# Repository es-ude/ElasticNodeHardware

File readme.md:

# Elastic Node Hardware Platform

## ENv5 - Elastic Node v5
The 5th generation of Elastic node is designed based on the 4th version, but with some improvements. The main improvements are:
- Using Cortex-M0 MCU instead of AVR 8-bit MCU, to gain more performance and lower power consumption.
- Using SPI as the communication interface between MCU and the FPGA to save more IO pins.
- Simplify the power supply circuit to reduce the space and improve reliability.
- Adding an energy meter chip to ease the energy measurement.
- Optimize the PCB layout to reduce the PCB size.

Before you start using the ENv5, please read the following documents accordingly:
- [ENv5 Test Version User Manual](v5/test_version/readme.md)
- [ENv5 Revision 1 User Manual](v5/revision_1/readme.md)

Troubleshooting
- When you notice the esp32 is not responding to the RP2040, you can apply the [pre-build firmware](v5/revision_1/prebuilds-firmware/test_esp_at.uf2) to test.
  - some descriptions about the behavior of the test are available [here](v5/revision_1/prebuilds-firmware/readme.md).

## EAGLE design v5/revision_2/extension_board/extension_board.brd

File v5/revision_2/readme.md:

# ENv5 Revision 2 User Manual

## Notice:
- The old wifi-shield is not compatible with the ENv5-Rev1. Please use the new extension board instead.
  - When you plug out the extension board, please try to make to PCBs in parallel to avoid damage to the male headers.
- Before you plug in a battery to the ENv5, please check if the order of the battery is correct.
  - The Cable close to the dot sign should be positive.
  - A thermal resistor should be attached to the battery to prevent the battery from overheating. If the resistor is not soldered, don't use the battery.
- The pin mapping of Env5 is referred to the [schematic of env5-rev2](en_v5_rev2_schematic.pdf).
- The pin mapping of the extension board is referred to the [schematic of extension board](extension_board/extension_board_schematic.pdf).

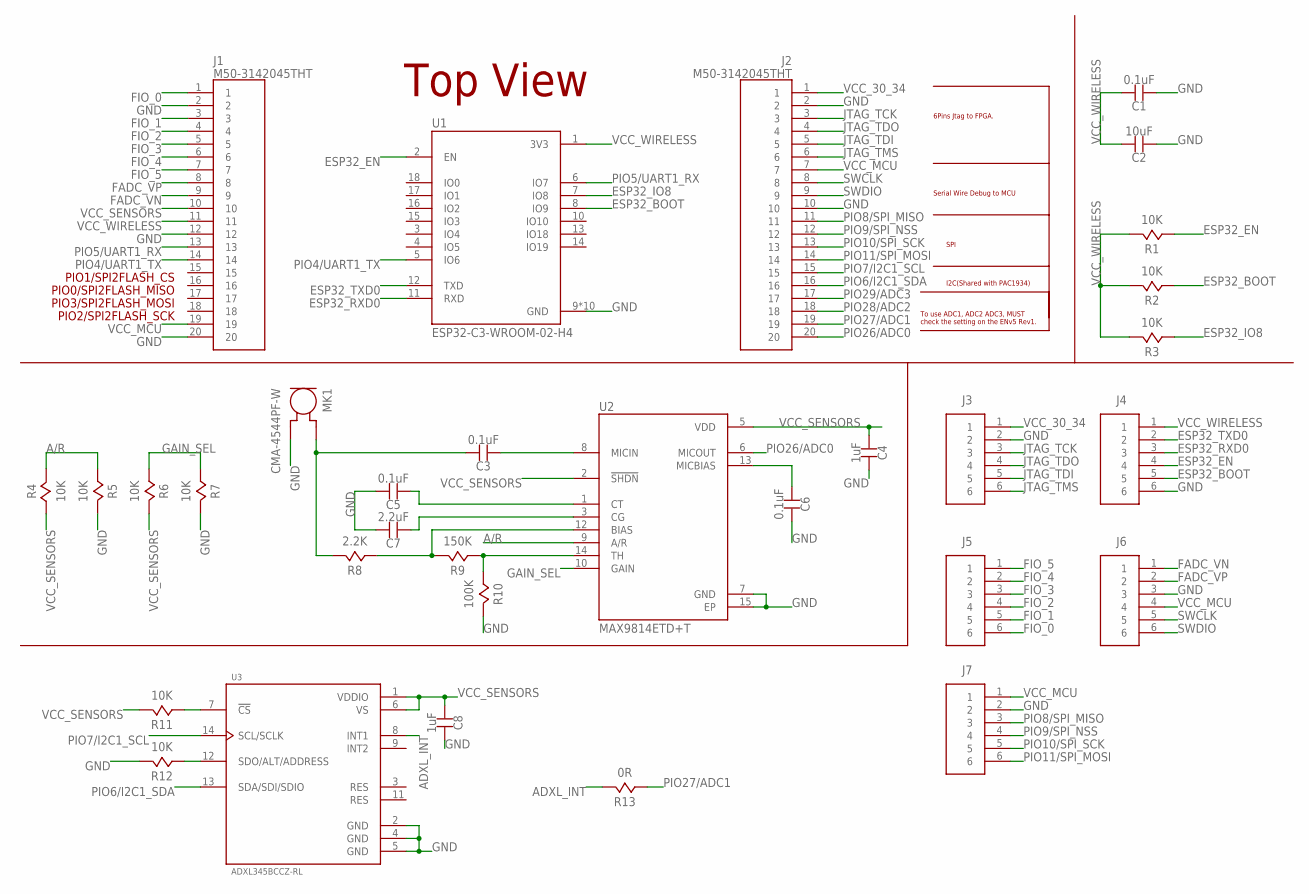
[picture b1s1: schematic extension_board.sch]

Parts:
C1, C3, C5, C6: 0.1uF; 0402
C2: 10uF; 0805
C4, C8: 1uF; 0402
C7: 2.2uF; 0402
J1, J2: M50-3142045THT; 20X1_HEADER_THT_1.27MM
J3, J4, J5, J6, J7: MALE_HEADER_6X1_2.54MM; HDR_6X1_2.54MM
MK1: CMA-4544PF-W; MIC_CMA-4544PF-W
R1, R2, R3, R4, R5, R6, R7, R11, R12: 10K; 0402
R8: 2.2K; 0402
R9: 150K; 0402
R10: 100K; 0402
R13: 0R; 0402
U1: ESP32-C3-WROOM-02-H4; MODULE_ESP32-C3-WROOM-02-H4
U2: MAX9814ETD+T; SON40P300X300X80-15N
U3: ADXL345BCCZ-RL; PQFN80P300X500X79-14N

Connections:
A/R: R4.2, R5.1, U2.9 (A/R)
ADXL_INT: R13.2, U3.8 (INT1)
ESP32_BOOT: J4.5, R2.1, U1.8 (IO9)
ESP32_EN: J4.4, R1.1, U1.2 (EN)
ESP32_IO8: R3.1, U1.7 (IO8)
ESP32_RXD0: J4.3, U1.11 (RXD)
ESP32_TXD0: J4.2, U1.12 (TXD)
FADC_VN: J1.9, J6.1
FADC_VP: J1.8, J6.2
FIO_0: J1.1, J5.6
FIO_1: J1.3, J5.5
FIO_2: J1.4, J5.4
FIO_3: J1.5, J5.3
FIO_4: J1.6, J5.2
FIO_5: J1.7, J5.1
GAIN_SEL: R6.1, R7.1, U2.10 (GAIN)
GND: C1.1, C2.1, C4.2, C5.2, C6.2, C7.2, C8.2, J1.2, J1.12, J1.20, J2.2, J2.10, J3.2, J4.6, J6.3, J7.2, MK1.2 (GND), R5.2, R7.2, R10.2, R12.2, U1.9 (GND), U1.19 (GND), U1.20 (GND), U1.21 (GND), U1.22 (GND), U1.23 (GND), U1.24 (GND), U1.25 (GND), U1.26 (GND), U1.27 (GND), U2.7 (GND), U2.15 (EP), U3.2 (GND), U3.4 (GND), U3.5 (GND)
JTAG_TCK: J2.3, J3.3
JTAG_TDI: J2.5, J3.5
JTAG_TDO: J2.4, J3.4
JTAG_TMS: J2.6, J3.6
MIC_INPUT: C3.2, MK1.1 (OUT), R8.2
unnamed: R11.1, U3.7 (!CS)
unnamed: R12.1, U3.12 (SDO/ALT/ADDRESS)
unnamed: C5.1, U2.1 (CT)
unnamed: C7.1, U2.3 (CG)
unnamed: C3.1, U2.8 (MICIN)
unnamed: R8.1, R9.2, U2.12 (BIAS)
unnamed: R9.1, R10.1, U2.14 (TH)
unnamed: C6.1, U2.13 (MICBIAS)
PIO4/UART1_TX: J1.14, U1.5 (IO6)
PIO5/UART1_RX: J1.13, U1.6 (IO7)
PIO6/I2C1_SDA: J2.16, U3.13 (SDA/SDI/SDIO)
PIO7/I2C1_SCL: J2.15, U3.14 (SCL/SCLK)
PIO8/SPI_MISO: J2.11, J7.3
PIO9/SPI_NSS: J2.12, J7.4
PIO10/SPI_SCK: J2.13, J7.5
PIO11/SPI_MOSI: J2.14, J7.6
PIO26/ADC0: J2.20, U2.6 (MICOUT)
PIO27/ADC1: J2.19, R13.1
PIO28/ADC2: J2.18
PIO29/ADC3: J2.17
SWCLK: J2.8, J6.5
SWDIO: J2.9, J6.6
VCC_30_34: J2.1, J3.1
VCC_MCU: J1.19, J2.7, J6.4, J7.1
VCC_SENSORS: C4.1, C8.1, J1.10, R4.1, R6.2, R11.2, U2.2 (!SHDN), U2.5 (VDD), U3.1 (VDDIO), U3.6 (VS)
VCC_WIRELESS: C1.2, C2.2, J1.11, J4.1, R1.2, R2.2, R3.2, U1.1 (3V3)

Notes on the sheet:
Top View
PIO1/SPI2FLASH_CS
PIO0/SPI2FLASH_MISO
PIO3/SPI2FLASH_MOSI
PIO2/SPI2FLASH_SCK
To use ADC1, ADC2 ADC3, MUST check the setting on the ENv5 Rev1.
6Pins Jtag to FPGA.
Serial Wire Debug to MCU
SPI
I2C(Shared with PAC1934)

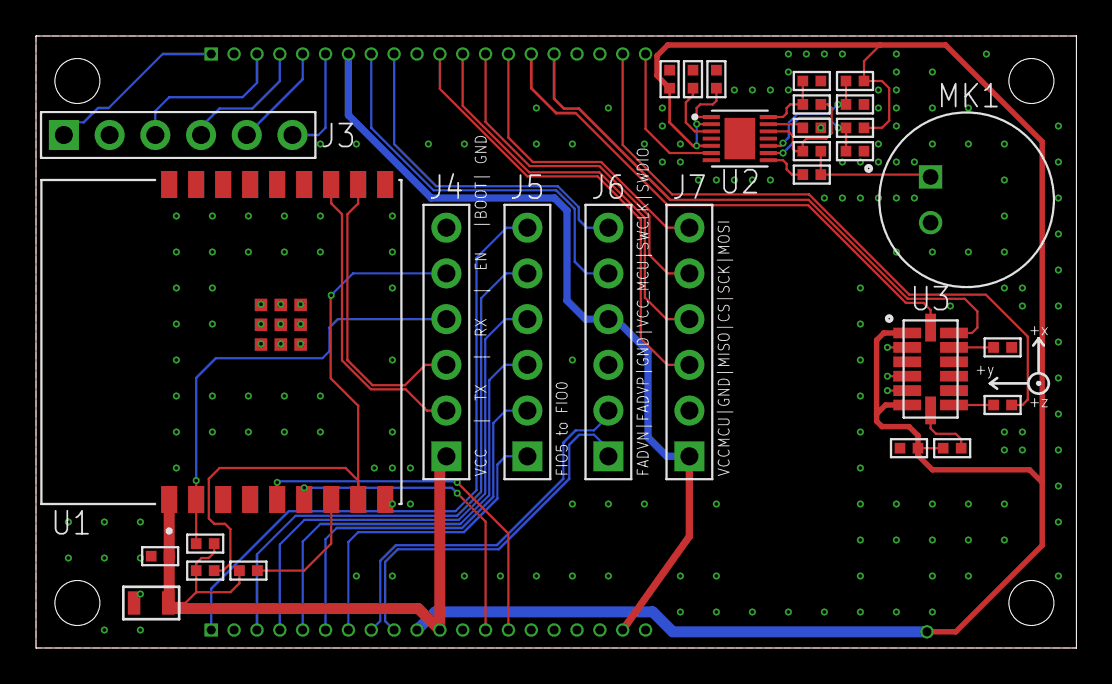
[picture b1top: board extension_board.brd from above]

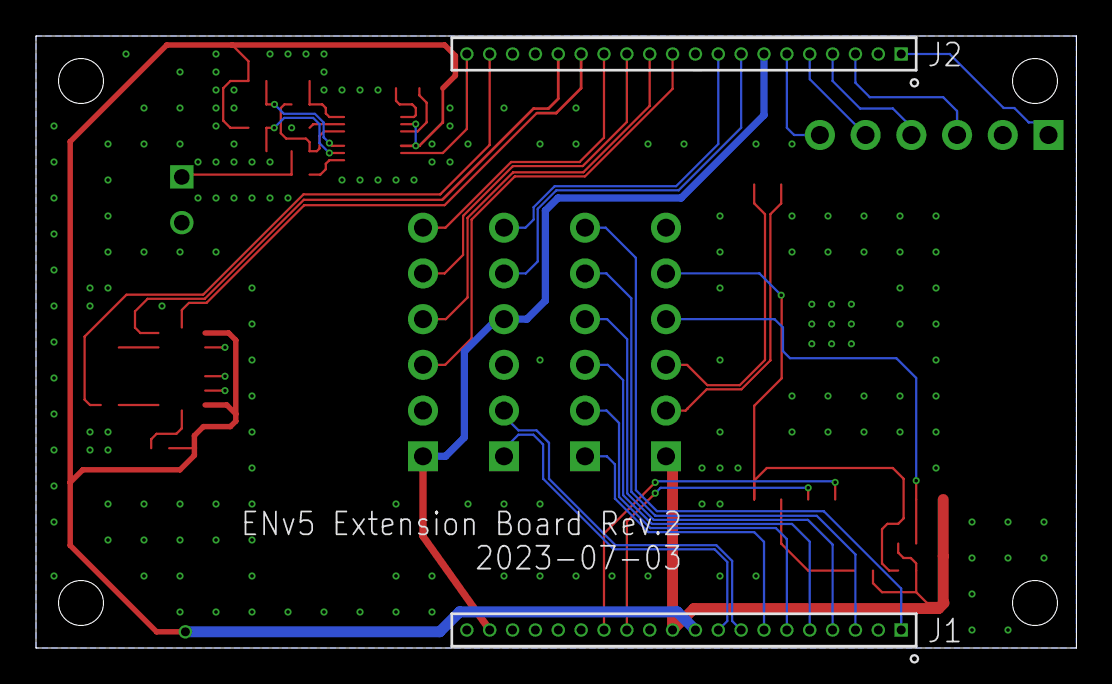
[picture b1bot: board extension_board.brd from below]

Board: 2 copper layers, 57.8 x 34.0 mm, 32 parts (2 on the bottom side), 46 nets.

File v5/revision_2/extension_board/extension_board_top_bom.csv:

Comment,Designator,Footprint,LCSC Part #
0.1uF,C1 C3 C5 C6,0402,
0R,R13,0402,
1uF,C4 C8,0402,
2.2K,R8,0402,
2.2uF,C7,0402,
10K,R1 R2 R3 R4 R5 R6 R7 R11 R12,0402,
10uF,C2,0805,
100K,R10,0402,
150K,R9,0402,
ADXL345BCCZ-RL,U3,PQFN80P300X500X79-14N,
ESP32-C3-WROOM-02-H4,U1,MODULE_ESP32-C3-WROOM-02-H4,
MAX9814ETD+T,U2,SON40P300X300X80-15N,

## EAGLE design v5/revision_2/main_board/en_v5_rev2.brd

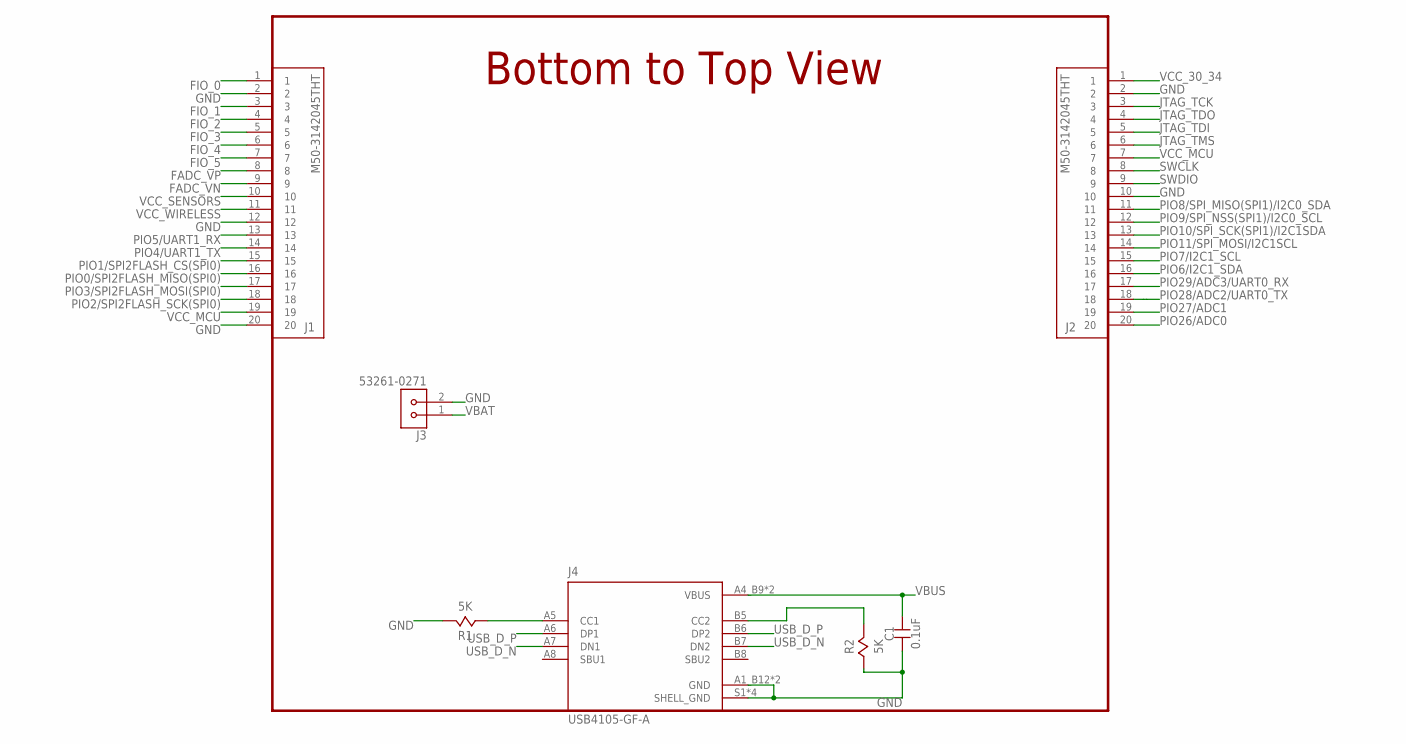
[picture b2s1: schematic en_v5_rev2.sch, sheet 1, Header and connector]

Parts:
C1: 0.1uF; 0805
J1, J2: M50-3142045THT; 20X1_HEADER_THT_1.27MM
J3: 53261-0271; MOLEX_53261-0271
J4: USB4105-GF-A; GCT_USB4105-GF-A
R1, R2: 5K; 0402

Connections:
FADC_VN: J1.9; also elsewhere on the board
FADC_VP: J1.8; also elsewhere on the board
FIO_0: J1.1; also elsewhere on the board
FIO_1: J1.3; also elsewhere on the board
FIO_2: J1.4; also elsewhere on the board
FIO_3: J1.5; also elsewhere on the board
FIO_4: J1.6; also elsewhere on the board
FIO_5: J1.7; also elsewhere on the board
GND: C1.1, J1.2, J1.12, J1.20, J2.2, J2.10, J3.2, J4.A1_B12 (GND), J4.B1_A12 (GND), J4.S1 (SHELL_GND), J4.S2 (SHELL_GND), J4.S3 (SHELL_GND), J4.S4 (SHELL_GND), R1.2, R2.1; also elsewhere on the board
JTAG_TCK: J2.3; also elsewhere on the board
JTAG_TDI: J2.5; also elsewhere on the board
JTAG_TDO: J2.4; also elsewhere on the board
JTAG_TMS: J2.6; also elsewhere on the board
unnamed: J4.B5 (CC2), R2.2
unnamed: J4.A5 (CC1), R1.1
PIO0/SPI2FLASH_MISO(SPI0): J1.16; also elsewhere on the board
PIO1/SPI2FLASH_CS(SPI0): J1.15; also elsewhere on the board
PIO2/SPI2FLASH_SCK(SPI0): J1.18; also elsewhere on the board
PIO3/SPI2FLASH_MOSI(SPI0): J1.17; also elsewhere on the board
PIO4/UART1_TX: J1.14; also elsewhere on the board
PIO5/UART1_RX: J1.13; also elsewhere on the board
PIO6/I2C1_SDA: J2.16; also elsewhere on the board
PIO7/I2C1_SCL: J2.15; also elsewhere on the board
PIO8/SPI_MISO(SPI1)/I2C0_SDA: J2.11; also elsewhere on the board
PIO9/SPI_NSS(SPI1)/I2C0_SCL: J2.12; also elsewhere on the board
PIO10/SPI_SCK(SPI1)/I2C1SDA: J2.13; also elsewhere on the board
PIO11/SPI_MOSI/I2C1SCL: J2.14; also elsewhere on the board
PIO26/ADC0: J2.20; also elsewhere on the board
PIO27/ADC1: J2.19; also elsewhere on the board
PIO28/ADC2/UART0_TX: J2.18; also elsewhere on the board
PIO29/ADC3/UART0_RX: J2.17; also elsewhere on the board
SWCLK: J2.8; also elsewhere on the board
SWDIO: J2.9; also elsewhere on the board
USB_D_N: J4.A7 (DN1), J4.B7 (DN2); also elsewhere on the board
USB_D_P: J4.A6 (DP1), J4.B6 (DP2); also elsewhere on the board
VBAT: J3.1; also elsewhere on the board
VBUS: C1.2, J4.A4_B9 (VBUS), J4.B4_A9 (VBUS); also elsewhere on the board
VCC_30_34: J2.1; also elsewhere on the board
VCC_MCU: J1.19, J2.7; also elsewhere on the board
VCC_SENSORS: J1.10; also elsewhere on the board
VCC_WIRELESS: J1.11; also elsewhere on the board

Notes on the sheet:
Bottom to Top View

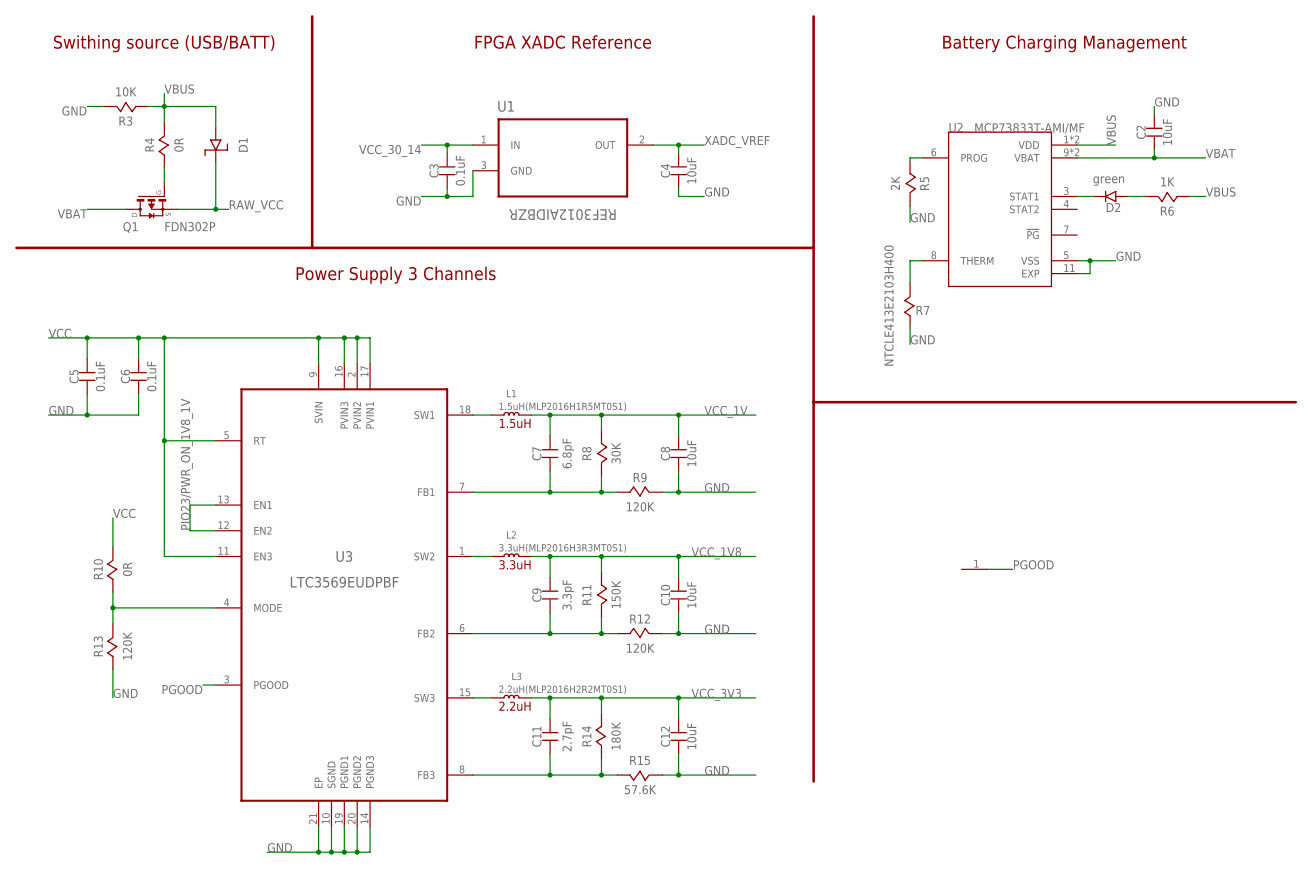
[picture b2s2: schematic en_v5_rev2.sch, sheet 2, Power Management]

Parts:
C2: 10uF; 0805
C3: 0.1uF; 0402
C4, C8, C10, C12: 10uF; CAPC1608-0603
C5, C6: 0.1uF; CAPC1608-0603
C7: 6.8pF; 0402
C9: 3.3pF; 0402
C11: 2.7pF; 0402
D1: DIODEB5817W; SOD-123
D2: green; 0402
L1: 1.5uH(MLP2016H1R5MT0S1); INDC2016X120N
L2: 3.3uH(MLP2016H3R3MT0S1); INDC2016X120N
L3: 2.2uH(MLP2016H2R2MT0S1); INDC2016X120N
Q1: FDN302P; SSOT-3
R3: 10K; 0402
R4, R10: 0R; 0402
R5: 2K; 0402
R6: 1K; 0402
R7: NTCLE413E2103H400; THT_2
R8: 30K; 0402
R9, R12, R13: 120K; 0402
R11: 150K; 0402
R14: 180K; 0402
R15: 57.6K; 0402
TP2: TEST_POINTSMD; SMD_PAD
U1: REF3012AIDBZR; SOT-23(3PIN)
U2: MCP73833T-AMI/MF; DFN-10(3X3X0.9)
U3: LTC3569EUDPBF; QFN40P300X300X80-21N

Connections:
GND: C2.2, C3.1, C4.1, C5.2, C6.2, C8.1, C10.2, C12.2, R3.2, R5.2, R7.P$1 (1), R9.2, R12.2, R13.1, R15.2, U1.3 (GND), U2.5 (VSS), U2.11 (EXP), U3.10 (SGND), U3.14 (PGND3), U3.19 (PGND1), U3.20 (PGND2), U3.21 (EP); also elsewhere on the board
unnamed: R7.P$2 (2), U2.8 (THERM)
unnamed: R5.1, U2.6 (PROG)
unnamed: Q1.1 (G), R4.1
unnamed: L2.1, U3.1 (SW2)
unnamed: L1.1, U3.18 (SW1)
unnamed: D2.2, U2.3 (STAT1)
unnamed: D2.1, R6.2
unnamed: C7.2, R8.2, R9.1, U3.7 (FB1)
unnamed: L3.2, U3.15 (SW3)
unnamed: C11.2, R14.2, R15.1, U3.8 (FB3)
unnamed: C9.2, R11.2, R12.1, U3.6 (FB2)
unnamed: R10.1, R13.2, U3.4 (MODE)
PGOOD: TP2.1, U3.3 (PGOOD)
PIO23/PWR_ON_1V8_1V: U3.12 (EN2), U3.13 (EN1); also elsewhere on the board
RAW_VCC: D1.1 (C), Q1.2 (S); also elsewhere on the board
VBAT: C2.1, Q1.3 (D), U2.9 (VBAT), U2.10 (VBAT); also elsewhere on the board
VBUS: D1.2 (A), R3.1, R4.2, R6.1, U2.1 (VDD), U2.2 (VDD); also elsewhere on the board
VCC: C5.1, C6.1, R10.2, U3.2 (PVIN2), U3.5 (RT), U3.9 (SVIN), U3.11 (EN3), U3.16 (PVIN3), U3.17 (PVIN1); also elsewhere on the board
VCC_1V: C7.1, C8.2, L1.2, R8.1; also elsewhere on the board
VCC_1V8: C9.1, C10.1, L2.2, R11.1; also elsewhere on the board
VCC_3V3: C11.1, C12.1, L3.1, R14.1; also elsewhere on the board
VCC_30_14: C3.2, U1.1 (IN); also elsewhere on the board
XADC_VREF: C4.2, U1.2 (OUT); also elsewhere on the board

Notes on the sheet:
1.5uH
3.3uH
2.2uH
Power Supply 3 Channels
Swithing source (USB/BATT)
FPGA XADC Reference
Battery Charging Management

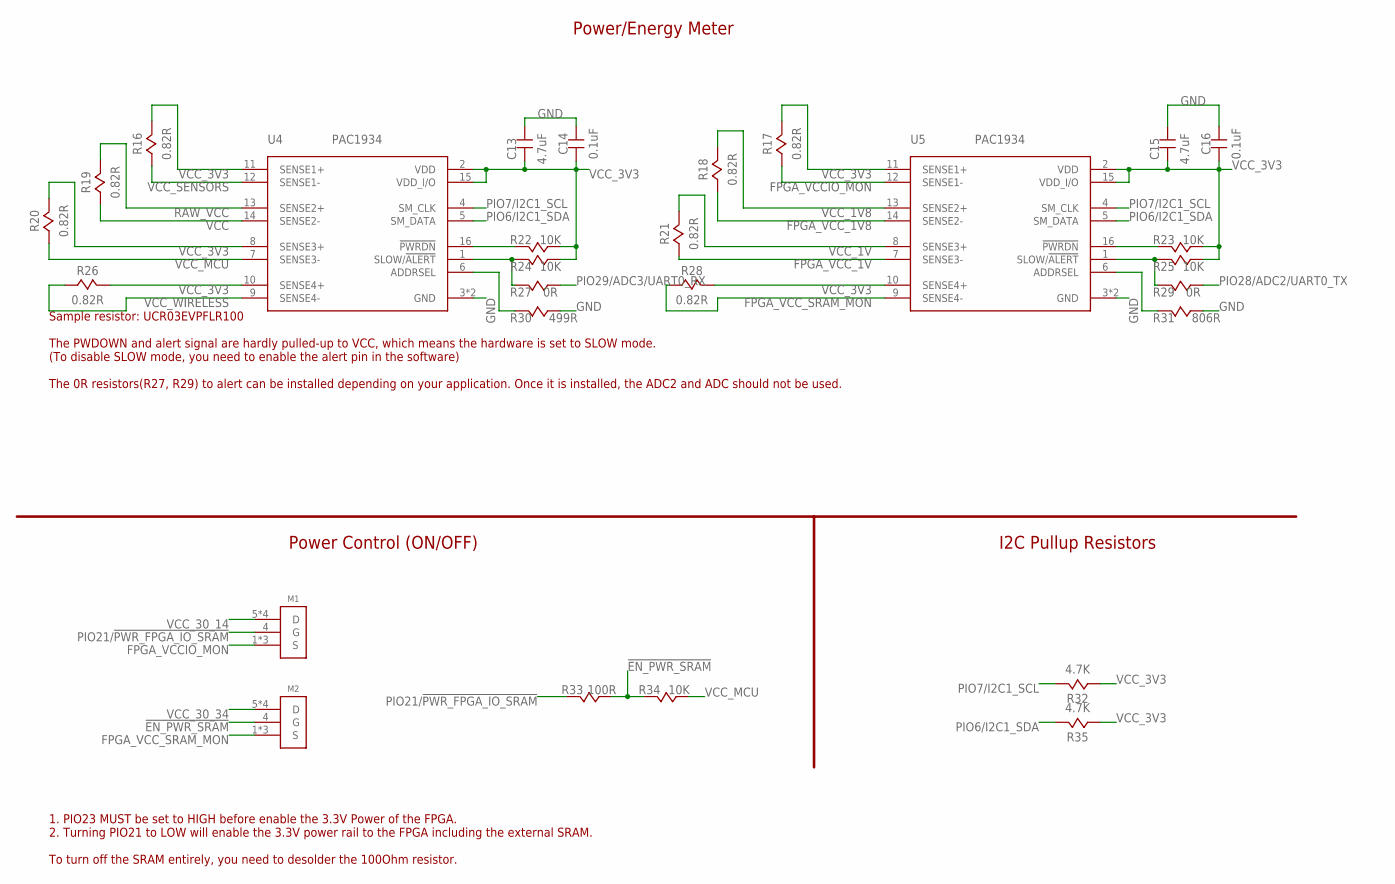
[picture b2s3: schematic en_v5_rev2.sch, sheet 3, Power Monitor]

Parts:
C13, C15: 4.7uF; CAPC1608-0603
C14, C16: 0.1uF; 0402
M1, M2: SISS23DN; POWERPAK1212-8
R16, R17, R18, R19, R20, R21, R26, R28: 0.82R; 0603
R22, R23, R24, R25, R34: 10K; 0402
R27, R29: 0R; 0402
R30: 499R; 0402
R31: 806R; 0402
R32, R35: 4.7K; 0402
R33: 100R; 0402
U4, U5: PAC1934; UQFN-16(4×4×0.5MM)

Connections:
!EN_PWR_SRAM: M2.4 (G), R33.1, R34.2
FPGA_VCCIO_MON: M1.1 (S), M1.2 (S), M1.3 (S), R17.1, U5.12 (SENSE1-)
FPGA_VCC_1V: R21.1, U5.7 (SENSE3-); also elsewhere on the board
FPGA_VCC_1V8: R18.1, U5.14 (SENSE2-); also elsewhere on the board
FPGA_VCC_SRAM_MON: M2.1 (S), M2.2 (S), M2.3 (S), R28.1, U5.9 (SENSE4-)
GND: C13.2, C14.2, C15.2, C16.2, R30.1, R31.1, U4.3 (GND), U4.17 (GND), U5.3 (GND), U5.17 (GND); also elsewhere on the board
unnamed: R24.2, R27.2, U4.1 (SLOW/!ALERT)
unnamed: R25.2, R29.2, U5.1 (SLOW/!ALERT)
unnamed: R22.2, U4.16 (!PWRDN)
unnamed: R30.2, U4.6 (ADDRSEL)
unnamed: R23.2, U5.16 (!PWRDN)
unnamed: R31.2, U5.6 (ADDRSEL)
PIO6/I2C1_SDA: R35.2, U4.5 (SM_DATA), U5.5 (SM_DATA); also elsewhere on the board
PIO7/I2C1_SCL: R32.2, U4.4 (SM_CLK), U5.4 (SM_CLK); also elsewhere on the board
PIO21/!PWR_FPGA_IO_SRAM: M1.4 (G), R33.2; also elsewhere on the board
PIO28/ADC2/UART0_TX: R29.1; also elsewhere on the board
PIO29/ADC3/UART0_RX: R27.1; also elsewhere on the board
RAW_VCC: R19.2, U4.13 (SENSE2+); also elsewhere on the board
VCC: R19.1, U4.14 (SENSE2-); also elsewhere on the board
VCC_1V: R21.2, U5.8 (SENSE3+); also elsewhere on the board
VCC_1V8: R18.2, U5.13 (SENSE2+); also elsewhere on the board
VCC_3V3: C13.1, C14.1, C15.1, C16.1, R16.2, R17.2, R20.2, R22.1, R23.1, R24.1, R25.1, R26.2, R28.2, R32.1, R35.1, U4.2 (VDD), U4.8 (SENSE3+), U4.10 (SENSE4+), U4.11 (SENSE1+), U4.15 (VDD_I/O), U5.2 (VDD), U5.10 (SENSE4+), U5.11 (SENSE1+), U5.15 (VDD_I/O); also elsewhere on the board
VCC_30_14: M1.5 (D), M1.6 (D), M1.7 (D), M1.8 (D); also elsewhere on the board
VCC_30_34: M2.5 (D), M2.6 (D), M2.7 (D), M2.8 (D); also elsewhere on the board
VCC_MCU: R20.1, R34.1, U4.7 (SENSE3-); also elsewhere on the board
VCC_SENSORS: R16.1, U4.12 (SENSE1-); also elsewhere on the board
VCC_WIRELESS: R26.1, U4.9 (SENSE4-); also elsewhere on the board

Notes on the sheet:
Sample resistor: UCR03EVPFLR100 The PWDOWN and alert signal are hardly pulled-up to VCC, which means the hardware is set to SLOW mode. (To disable SLOW mode, you need to enable the alert pin in the software) The 0R resistors(R27, R29) to alert can be installed depending on your application. Once it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
Power/Energy Meter
Power Control (ON/OFF)
I2C Pullup Resistors
1. PIO23 MUST be set to HIGH before enable the 3.3V Power of the FPGA. 2. Turning PIO21 to LOW will enable the 3.3V power rail to the FPGA including the external SRAM. To turn off the SRAM entirely, you need to desolder the 100Ohm resistor.

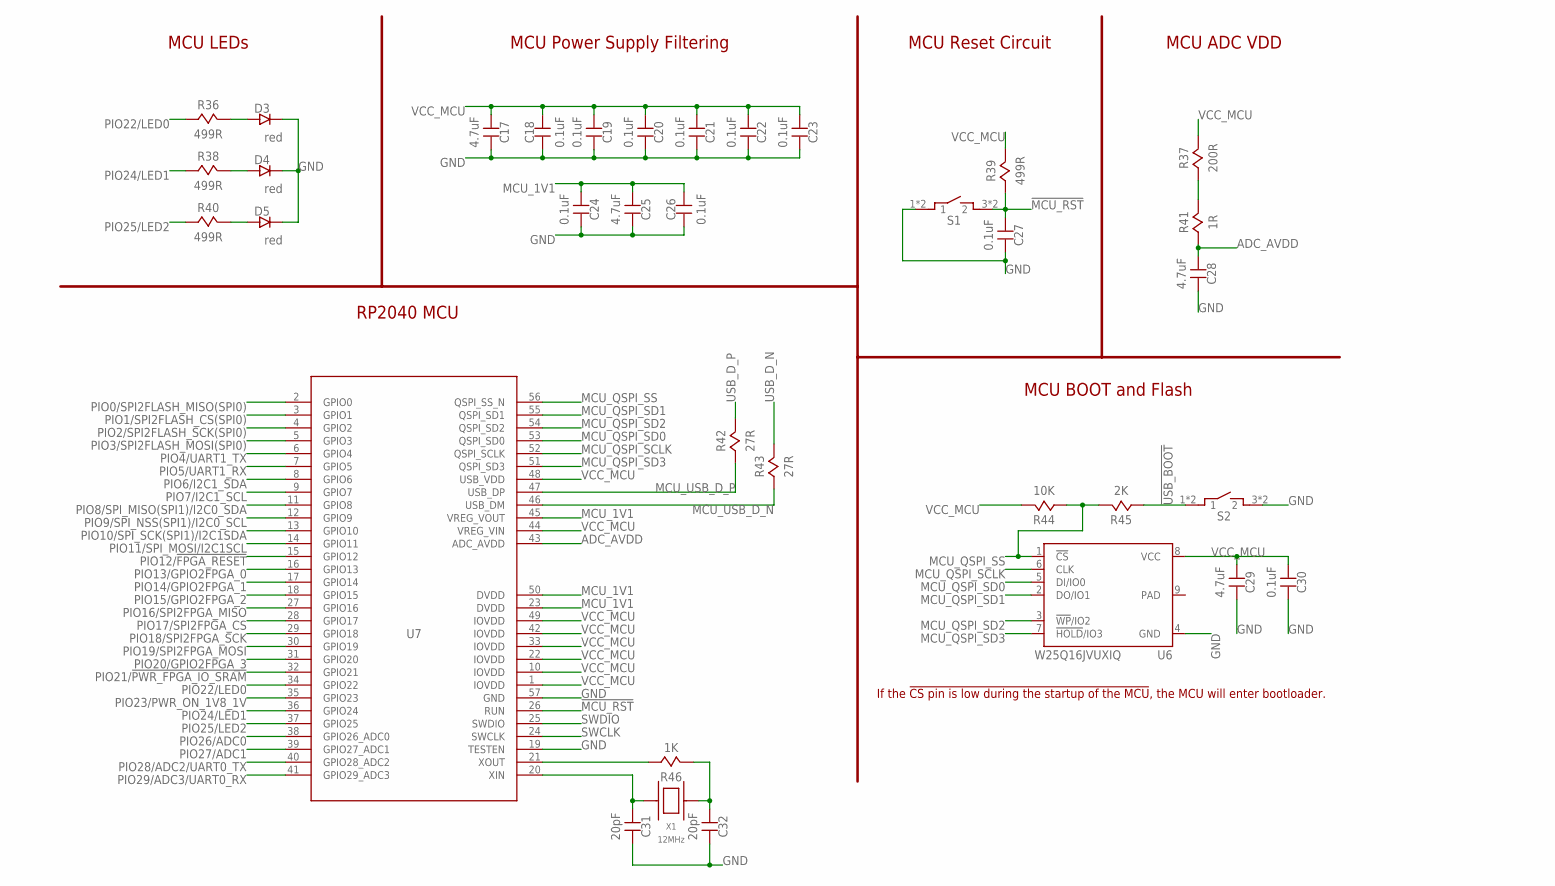
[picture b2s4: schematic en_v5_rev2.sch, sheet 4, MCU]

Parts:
C17, C25, C28, C29: 4.7uF; CAPC1608-0603
C18, C19, C20, C21, C22, C23, C24, C26, C27, C30: 0.1uF; 0402
C31, C32: 20pF; 0402
D3, D4, D5: red; 0402
R36, R38, R39, R40: 499R; 0402
R37: 200R; 0402
R41: 1R; 0402
R42, R43: 27R; 0402
R44: 10K; 0402
R45: 2K; 0402
R46: 1K; 0402
S1, S2: TACTILE-SWITCH
U6: W25Q16JVUXIQ; USON8-2X3MM
U7: RP2040; QFN40P700X700X100-57T310N
X1: 12MHz; 3.2X2.5_OSC

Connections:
!MCU_RST: C27.1, R39.1, S1.3 (2), S1.4 (2), U7.26 (RUN)
!USB_BOOT: R45.1, S2.1, S2.2 (1)
ADC_AVDD: C28.1, R41.1, U7.43 (ADC_AVDD)
ADC_VREF: R37.1, R41.2
GND: C17.2, C18.1, C19.2, C20.2, C21.2, C22.2, C23.2, C24.2, C25.2, C26.1, C27.2, C28.2, C29.2, C30.2, C31.2, C32.2, D3.2, D4.2, D5.2, S1.1, S1.2 (1), S2.3 (2), S2.4 (2), U6.4 (GND), U7.19 (TESTEN), U7.57 (GND); also elsewhere on the board
MCU_1V1: C24.1, C25.1, C26.2, U7.23 (DVDD), U7.45 (VREG_VOUT), U7.50 (DVDD)
MCU_QSPI_SCLK: U6.6 (CLK), U7.52 (QSPI_SCLK)
MCU_QSPI_SD0: U6.5 (DI/IO0), U7.53 (QSPI_SD0)
MCU_QSPI_SD1: U6.2 (DO/IO1), U7.55 (QSPI_SD1)
MCU_QSPI_SD2: U6.3 (!WP!/IO2), U7.54 (QSPI_SD2)
MCU_QSPI_SD3: U6.7 (!HOLD!/IO3), U7.51 (QSPI_SD3)
MCU_QSPI_SS: R44.1, R45.2, U6.1 (!CS), U7.56 (QSPI_SS_N)
MCU_USB_D_N: R43.1, U7.46 (USB_DM)
MCU_USB_D_P: R42.1, U7.47 (USB_DP)
unnamed: R46.1, U7.21 (XOUT)
unnamed: C32.1, R46.2, X1.3
unnamed: C31.1, U7.20 (XIN), X1.1
unnamed: D3.1, R36.2
unnamed: D4.1, R38.2
unnamed: D5.1, R40.2
PIO0/SPI2FLASH_MISO(SPI0): U7.2 (GPIO0); also elsewhere on the board
PIO1/SPI2FLASH_CS(SPI0): U7.3 (GPIO1); also elsewhere on the board
PIO2/SPI2FLASH_SCK(SPI0): U7.4 (GPIO2); also elsewhere on the board
PIO3/SPI2FLASH_MOSI(SPI0): U7.5 (GPIO3); also elsewhere on the board
PIO4/UART1_TX: U7.6 (GPIO4); also elsewhere on the board
PIO5/UART1_RX: U7.7 (GPIO5); also elsewhere on the board
PIO6/I2C1_SDA: U7.8 (GPIO6); also elsewhere on the board
PIO7/I2C1_SCL: U7.9 (GPIO7); also elsewhere on the board
PIO8/SPI_MISO(SPI1)/I2C0_SDA: U7.11 (GPIO8); also elsewhere on the board
PIO9/SPI_NSS(SPI1)/I2C0_SCL: U7.12 (GPIO9); also elsewhere on the board
PIO10/SPI_SCK(SPI1)/I2C1SDA: U7.13 (GPIO10); also elsewhere on the board
PIO11/SPI_MOSI/I2C1SCL: U7.14 (GPIO11); also elsewhere on the board
PIO12/!FPGA_RESET: U7.15 (GPIO12); also elsewhere on the board
PIO13/GPIO2FPGA_0: U7.16 (GPIO13); also elsewhere on the board
PIO14/GPIO2FPGA_1: U7.17 (GPIO14); also elsewhere on the board
PIO15/GPIO2FPGA_2: U7.18 (GPIO15); also elsewhere on the board
PIO16/SPI2FPGA_MISO: U7.27 (GPIO16); also elsewhere on the board
PIO17/SPI2FPGA_CS: U7.28 (GPIO17); also elsewhere on the board
PIO18/SPI2FPGA_SCK: U7.29 (GPIO18); also elsewhere on the board
PIO19/SPI2FPGA_MOSI: U7.30 (GPIO19); also elsewhere on the board
PIO20/GPIO2FPGA_3: U7.31 (GPIO20); also elsewhere on the board
PIO21/!PWR_FPGA_IO_SRAM: U7.32 (GPIO21); also elsewhere on the board
PIO22/LED0: R36.1, U7.34 (GPIO22)
PIO23/PWR_ON_1V8_1V: U7.35 (GPIO23); also elsewhere on the board
PIO24/LED1: R38.1, U7.36 (GPIO24)
PIO25/LED2: R40.1, U7.37 (GPIO25)
PIO26/ADC0: U7.38 (GPIO26_ADC0); also elsewhere on the board
PIO27/ADC1: U7.39 (GPIO27_ADC1); also elsewhere on the board
PIO28/ADC2/UART0_TX: U7.40 (GPIO28_ADC2); also elsewhere on the board
PIO29/ADC3/UART0_RX: U7.41 (GPIO29_ADC3); also elsewhere on the board
SWCLK: U7.24 (SWCLK); also elsewhere on the board
SWDIO: U7.25 (SWDIO); also elsewhere on the board
USB_D_N: R43.2; also elsewhere on the board
USB_D_P: R42.2; also elsewhere on the board
VCC_MCU: C17.1, C18.2, C19.1, C20.1, C21.1, C22.1, C23.1, C29.1, C30.1, R37.2, R39.2, R44.2, U6.8 (VCC), U7.1 (IOVDD), U7.10 (IOVDD), U7.22 (IOVDD), U7.33 (IOVDD), U7.42 (IOVDD), U7.44 (VREG_VIN), U7.48 (USB_VDD), U7.49 (IOVDD); also elsewhere on the board

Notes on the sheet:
If the !CS pin is low during the startup of the MCU, the MCU will enter bootloader.
MCU LEDs
RP2040 MCU
MCU Power Supply Filtering
MCU Reset Circuit
MCU ADC VDD
MCU BOOT and Flash

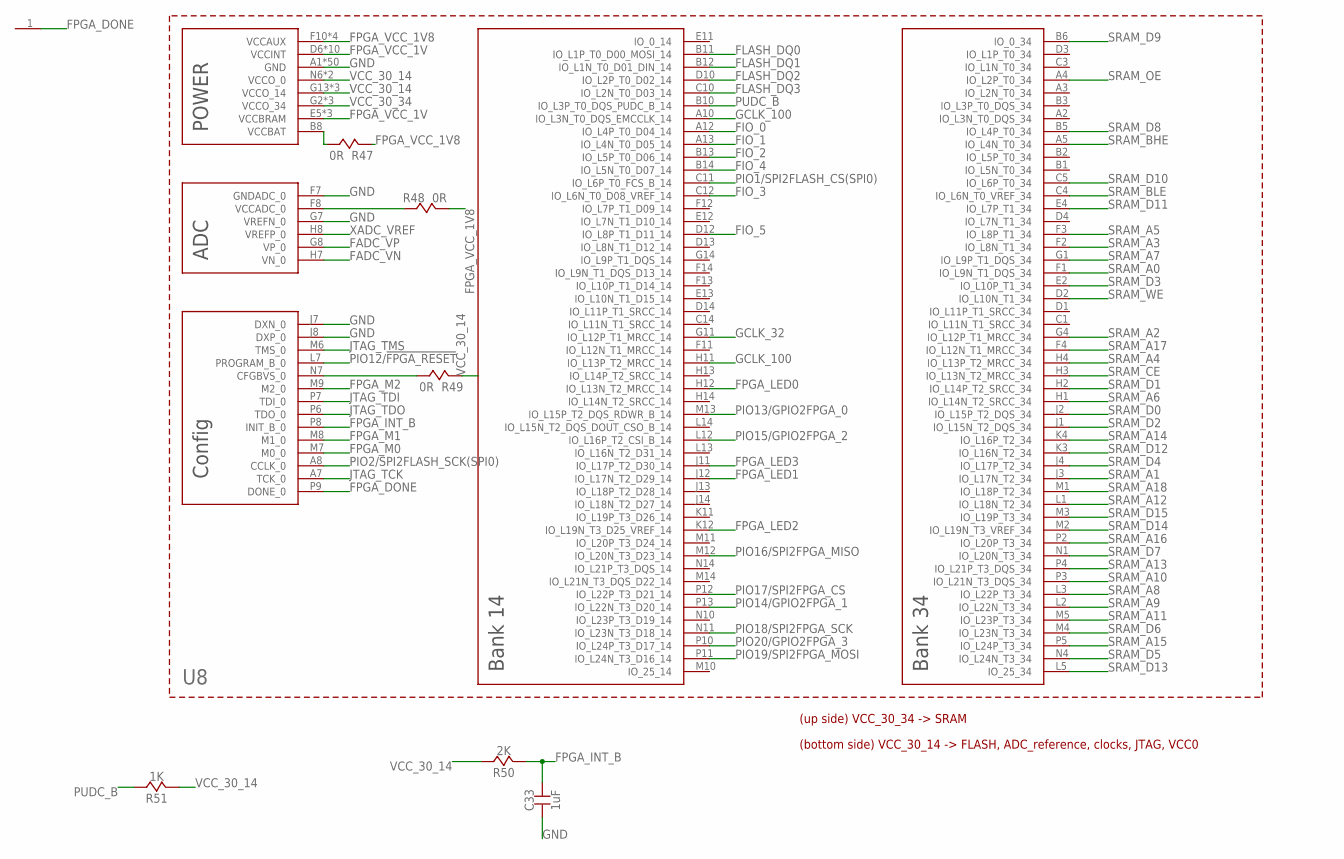
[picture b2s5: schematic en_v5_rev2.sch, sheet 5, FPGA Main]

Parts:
C33: 1uF; 0402
R47, R48, R49: 0R; 0402
R50: 2K; 0402
R51: 1K; 0402
TP1: TEST_POINTSMD; SMD_PAD
U8: SPARTAN7-LX15; FTGB196

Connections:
FADC_VN: U8.H7 (VN_0); also elsewhere on the board
FADC_VP: U8.G8 (VP_0); also elsewhere on the board
FIO_0: U8.A12 (IO_L4P_T0_D04_14); also elsewhere on the board
FIO_1: U8.A13 (IO_L4N_T0_D05_14); also elsewhere on the board
FIO_2: U8.B13 (IO_L5P_T0_D06_14); also elsewhere on the board
FIO_3: U8.C12 (IO_L6N_T0_D08_VREF_14); also elsewhere on the board
FIO_4: U8.B14 (IO_L5N_T0_D07_14); also elsewhere on the board
FIO_5: U8.D12 (IO_L8P_T1_D11_14); also elsewhere on the board
FLASH_DQ0: U8.B11 (IO_L1P_T0_D00_MOSI_14); also elsewhere on the board
FLASH_DQ1: U8.B12 (IO_L1N_T0_D01_DIN_14); also elsewhere on the board
FLASH_DQ2: U8.D10 (IO_L2P_T0_D02_14); also elsewhere on the board
FLASH_DQ3: U8.C10 (IO_L2N_T0_D03_14); also elsewhere on the board
FPGA_DONE: TP1.1, U8.P9 (DONE_0)
FPGA_INT_B: C33.2, R50.2, U8.P8 (INIT_B_0)
FPGA_LED0: U8.H12 (IO_L13N_T2_MRCC_14); also elsewhere on the board
FPGA_LED1: U8.J12 (IO_L17N_T2_D29_14); also elsewhere on the board
FPGA_LED2: U8.K12 (IO_L19N_T3_D25_VREF_14); also elsewhere on the board
FPGA_LED3: U8.J11 (IO_L17P_T2_D30_14); also elsewhere on the board
FPGA_M0: U8.M7 (M0_0); also elsewhere on the board
FPGA_M1: U8.M8 (M1_0); also elsewhere on the board
FPGA_M2: U8.M9 (M2_0); also elsewhere on the board
FPGA_VCC_1V: U8.D6 (VCCINT), U8.D8 (VCCINT), U8.E5 (VCCBRAM), U8.E7 (VCCINT), U8.E9 (VCCINT), U8.F6 (VCCINT), U8.G5 (VCCBRAM), U8.G9 (VCCINT), U8.H6 (VCCINT), U8.J5 (VCCBRAM), U8.J9 (VCCINT), U8.K6 (VCCINT), U8.K8 (VCCINT); also elsewhere on the board
FPGA_VCC_1V8: R47.2, R48.2, U8.F10 (VCCAUX), U8.H10 (VCCAUX), U8.K10 (VCCAUX), U8.L9 (VCCAUX); also elsewhere on the board
GCLK_32: U8.G11 (IO_L12P_T1_MRCC_14); also elsewhere on the board
GCLK_100: U8.A10 (IO_L3N_T0_DQS_EMCCLK_14), U8.H11 (IO_L13P_T2_MRCC_14); also elsewhere on the board
GND: C33.1, U8.A1 (GND), U8.A6 (GND), U8.A9 (GND), U8.A11 (GND), U8.A14 (GND), U8.B4 (GND), U8.B7 (GND), U8.B9 (GND), U8.C2 (GND), U8.C6 (GND), U8.C7 (GND), U8.C8 (GND), U8.C9 (GND), U8.C13 (GND), U8.D5 (GND), U8.D7 (GND), U8.D9 (GND), U8.D11 (GND), U8.E1 (GND), U8.E3 (GND), U8.E6 (GND), U8.E8 (GND), U8.E10 (GND), U8.E14 (GND), U8.F5 (GND), U8.F7 (GNDADC_0), U8.F9 (GND), U8.G3 (GND), U8.G6 (GND), U8.G7 (VREFN_0), U8.G10 (GND), U8.G12 (GND), U8.H5 (GND), U8.H9 (GND), U8.J6 (GND), U8.J7 (DXN_0), U8.J8 (DXP_0), U8.J10 (GND), U8.K1 (GND), U8.K5 (GND), U8.K7 (GND), U8.K9 (GND), U8.K14 (GND), U8.L4 (GND), U8.L6 (GND), U8.L8 (GND), U8.L10 (GND), U8.L11 (GND), U8.N3 (GND), U8.N5 (GND), U8.N9 (GND), U8.N12 (GND), U8.P1 (GND), U8.P14 (GND); also elsewhere on the board
JTAG_TCK: U8.A7 (TCK_0); also elsewhere on the board
JTAG_TDI: U8.P7 (TDI_0); also elsewhere on the board
JTAG_TDO: U8.P6 (TDO_0); also elsewhere on the board
JTAG_TMS: U8.M6 (TMS_0); also elsewhere on the board
unnamed: R47.1, U8.B8 (VCCBAT)
unnamed: R49.1, U8.N7 (CFGBVS_0)
unnamed: R48.1, U8.F8 (VCCADC_0)
PIO1/SPI2FLASH_CS(SPI0): U8.C11 (IO_L6P_T0_FCS_B_14); also elsewhere on the board
PIO2/SPI2FLASH_SCK(SPI0): U8.A8 (CCLK_0); also elsewhere on the board
PIO12/!FPGA_RESET: U8.L7 (PROGRAM_B_0); also elsewhere on the board
PIO13/GPIO2FPGA_0: U8.M13 (IO_L15P_T2_DQS_RDWR_B_14); also elsewhere on the board
PIO14/GPIO2FPGA_1: U8.P13 (IO_L22N_T3_D20_14); also elsewhere on the board
PIO15/GPIO2FPGA_2: U8.L12 (IO_L16P_T2_CSI_B_14); also elsewhere on the board
PIO16/SPI2FPGA_MISO: U8.M12 (IO_L20N_T3_D23_14); also elsewhere on the board
PIO17/SPI2FPGA_CS: U8.P12 (IO_L22P_T3_D21_14); also elsewhere on the board
PIO18/SPI2FPGA_SCK: U8.N11 (IO_L23N_T3_D18_14); also elsewhere on the board
PIO19/SPI2FPGA_MOSI: U8.P11 (IO_L24N_T3_D16_14); also elsewhere on the board
PIO20/GPIO2FPGA_3: U8.P10 (IO_L24P_T3_D17_14); also elsewhere on the board
PUDC_B: R51.1, U8.B10 (IO_L3P_T0_DQS_PUDC_B_14)
SRAM_A0: U8.F1 (IO_L9N_T1_DQS_34); also elsewhere on the board
SRAM_A1: U8.J3 (IO_L17N_T2_34); also elsewhere on the board
SRAM_A2: U8.G4 (IO_L12P_T1_MRCC_34); also elsewhere on the board
SRAM_A3: U8.F2 (IO_L8N_T1_34); also elsewhere on the board
SRAM_A4: U8.H4 (IO_L13P_T2_MRCC_34); also elsewhere on the board
SRAM_A5: U8.F3 (IO_L8P_T1_34); also elsewhere on the board
SRAM_A6: U8.H1 (IO_L14N_T2_SRCC_34); also elsewhere on the board
SRAM_A7: U8.G1 (IO_L9P_T1_DQS_34); also elsewhere on the board
SRAM_A8: U8.L3 (IO_L22P_T3_34); also elsewhere on the board
SRAM_A9: U8.L2 (IO_L22N_T3_34); also elsewhere on the board
SRAM_A10: U8.P3 (IO_L21N_T3_DQS_34); also elsewhere on the board
SRAM_A11: U8.M5 (IO_L23P_T3_34); also elsewhere on the board
SRAM_A12: U8.L1 (IO_L18N_T2_34); also elsewhere on the board
SRAM_A13: U8.P4 (IO_L21P_T3_DQS_34); also elsewhere on the board
SRAM_A14: U8.K4 (IO_L16P_T2_34); also elsewhere on the board
SRAM_A15: U8.P5 (IO_L24P_T3_34); also elsewhere on the board
SRAM_A16: U8.P2 (IO_L20P_T3_34); also elsewhere on the board
SRAM_A17: U8.F4 (IO_L12N_T1_MRCC_34); also elsewhere on the board
SRAM_A18: U8.M1 (IO_L18P_T2_34); also elsewhere on the board
SRAM_BHE: U8.A5 (IO_L4N_T0_34); also elsewhere on the board
SRAM_BLE: U8.C4 (IO_L6N_T0_VREF_34); also elsewhere on the board
SRAM_CE: U8.H3 (IO_L13N_T2_MRCC_34); also elsewhere on the board
SRAM_D0: U8.J2 (IO_L15P_T2_DQS_34); also elsewhere on the board
SRAM_D1: U8.H2 (IO_L14P_T2_SRCC_34); also elsewhere on the board
SRAM_D2: U8.J1 (IO_L15N_T2_DQS_34); also elsewhere on the board
SRAM_D3: U8.E2 (IO_L10P_T1_34); also elsewhere on the board
SRAM_D4: U8.J4 (IO_L17P_T2_34); also elsewhere on the board
SRAM_D5: U8.N4 (IO_L24N_T3_34); also elsewhere on the board
SRAM_D6: U8.M4 (IO_L23N_T3_34); also elsewhere on the board
SRAM_D7: U8.N1 (IO_L20N_T3_34); also elsewhere on the board
SRAM_D8: U8.B5 (IO_L4P_T0_34); also elsewhere on the board
SRAM_D9: U8.B6 (IO_0_34); also elsewhere on the board
SRAM_D10: U8.C5 (IO_L6P_T0_34); also elsewhere on the board
SRAM_D11: U8.E4 (IO_L7P_T1_34); also elsewhere on the board
SRAM_D12: U8.K3 (IO_L16N_T2_34); also elsewhere on the board
SRAM_D13: U8.L5 (IO_25_34); also elsewhere on the board
SRAM_D14: U8.M2 (IO_L19N_T3_VREF_34); also elsewhere on the board
SRAM_D15: U8.M3 (IO_L19P_T3_34); also elsewhere on the board
SRAM_OE: U8.A4 (IO_L2P_T0_34); also elsewhere on the board
SRAM_WE: U8.D2 (IO_L10N_T1_34); also elsewhere on the board
VCC_30_14: R49.2, R50.1, R51.2, U8.G13 (VCCO_14), U8.K13 (VCCO_14), U8.N6 (VCCO_0), U8.N8 (VCCO_0), U8.N13 (VCCO_14); also elsewhere on the board
VCC_30_34: U8.G2 (VCCO_34), U8.K2 (VCCO_34), U8.N2 (VCCO_34); also elsewhere on the board
XADC_VREF: U8.H8 (VREFP_0); also elsewhere on the board

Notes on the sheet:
(up side) VCC_30_34 -> SRAM
(bottom side) VCC_30_14 -> FLASH, ADC_reference, clocks, JTAG, VCC0
